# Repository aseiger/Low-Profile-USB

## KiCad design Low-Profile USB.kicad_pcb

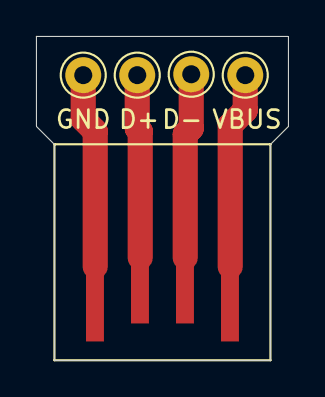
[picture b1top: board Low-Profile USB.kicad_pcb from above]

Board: 2 copper layers, 14.0 x 18.0 mm, 5 parts (0 on the bottom side), 4 nets.

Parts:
H1: VBUS; Pin_D1.0mm_L10.0mm
H2: D+; Pin_D1.0mm_L10.0mm
H3: D-; Pin_D1.0mm_L10.0mm
H4: GND; Pin_D1.0mm_L10.0mm
J1: USB_A; PCB_USB

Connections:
unnamed: H1.1, J1.1
unnamed: H2.1, J1.3
unnamed: H3.1, J1.2
unnamed: H4.1, J1.4, J1.5
